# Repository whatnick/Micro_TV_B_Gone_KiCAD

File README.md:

# Micro TV-B-Gone

KiCAD port of the [Micro TV-B-Gone](https://hackaday.io/project/29330-micro-tv-b-gone) by Nicholas Junker. Designed to be used with [ring based emitters](https://hackaday.io/project/29330-micro-tv-b-gone) eventually.

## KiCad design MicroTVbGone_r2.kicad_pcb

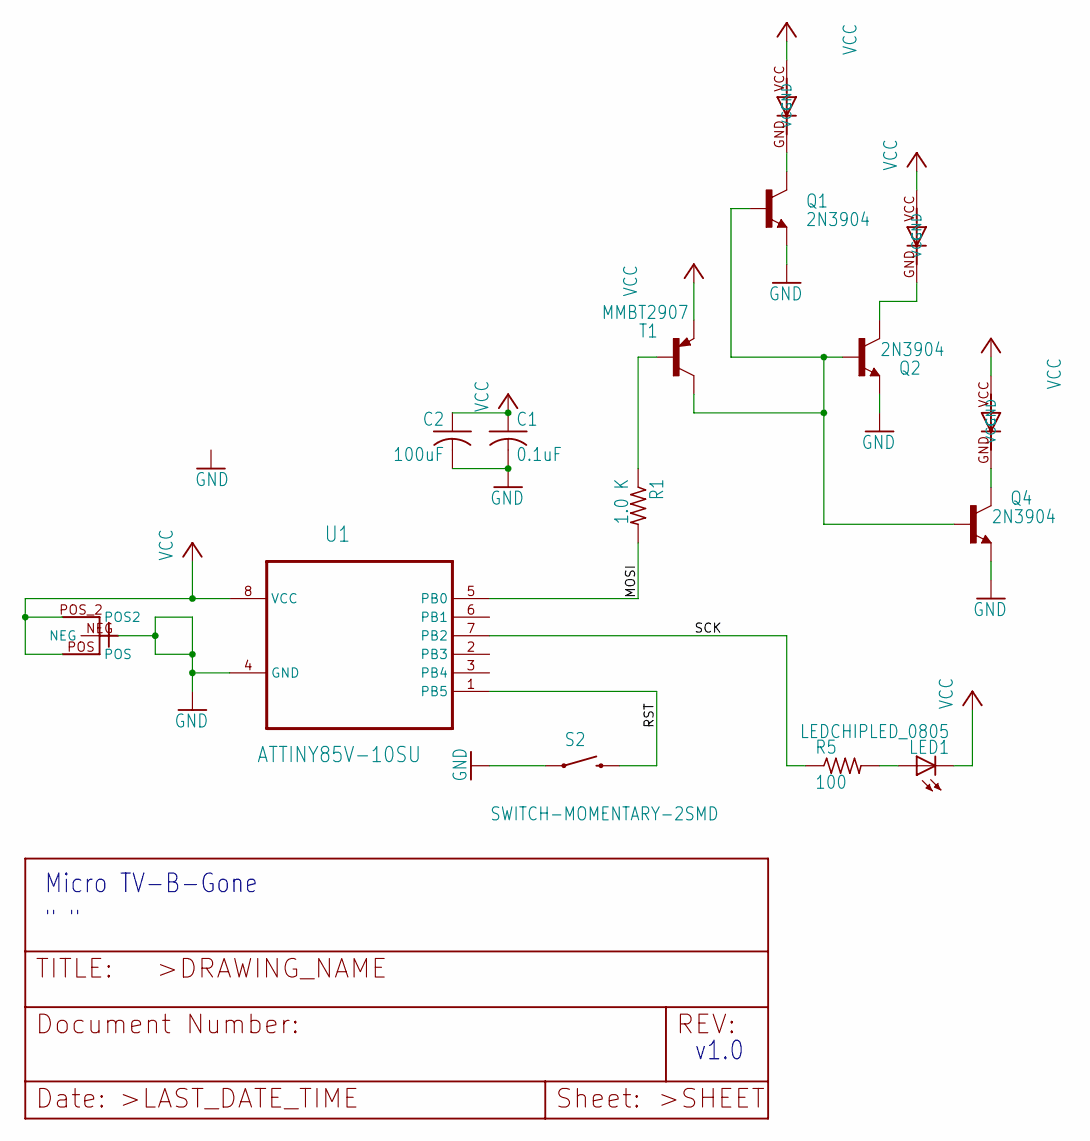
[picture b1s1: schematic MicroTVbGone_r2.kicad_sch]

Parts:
C1: 0.1uF; C0805
C2: 100uF; C0805
J1: 712-BAT-HLD-001; 20MM_COINCELL
LED1: LEDCHIPLED_0805; CHIPLED_0805
Q1, Q2, Q4: 2N3904; SOT23
R1: 1.0 K; R0805
R5: 100; R0805
S2: SWITCH-MOMENTARY-2SMD; TACTILE-SWITCH-SMD
T1: MMBT2907; SOT23-BEC
U1: ATTINY85V-10SU; SOIC127P798X216-8N
U$2, U$3, U$4: SFH4646-ZSFH4646; MIDLED

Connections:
GND: C1.2, C2.2, J1.NEG, Q1.2 (E), Q2.2 (E), Q4.2 (E), S2.1, U1.4 (GND); also elsewhere on the board
MOSI: R1.2, U1.5 (PB0)
unnamed: LED1.A, R5.2
unnamed: Q2.3 (C), U$2.GND
unnamed: Q4.3 (C), U$4.GND
unnamed: Q1.1 (B), Q2.1 (B), Q4.1 (B), T1.C
unnamed: Q1.3 (C), U$3.GND
unnamed: R1.1, T1.B
RST: S2.3 (2), U1.1 (PB5)
SCK: R5.1, U1.7 (PB2)
VCC: C1.1, C2.1, J1.POS, J1.POS_2 (POS2), LED1.C, T1.E, U1.8 (VCC), U$2.VCC, U$3.VCC, U$4.VCC; also elsewhere on the board

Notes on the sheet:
Micro TV-B-Gone
v1.0
" "

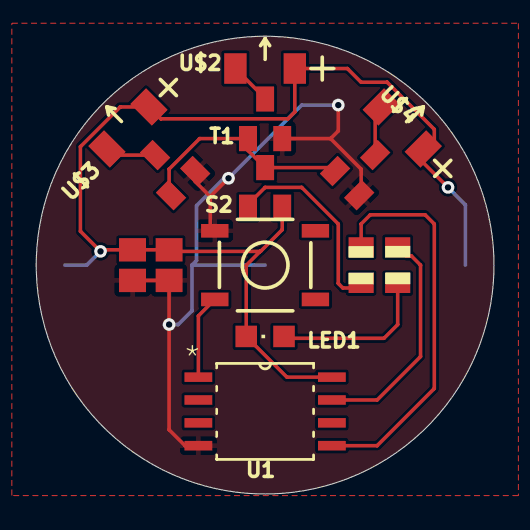
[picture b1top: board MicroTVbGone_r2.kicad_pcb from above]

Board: 2 copper layers, 25.4 x 25.4 mm, 15 parts (1 on the bottom side), 11 nets.

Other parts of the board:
U$1: 712-BAT-HLD-001; 20MM_COINCELL

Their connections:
GND: U$1.NEG; also elsewhere on the board
VCC: U$1.POS, U$1.POS_2; also elsewhere on the board

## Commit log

2022-11-07 Imported from EAGLE
2022-11-07 Reduce stackup to 2 layers and export Gerbers
2022-11-07 Export gerbers
